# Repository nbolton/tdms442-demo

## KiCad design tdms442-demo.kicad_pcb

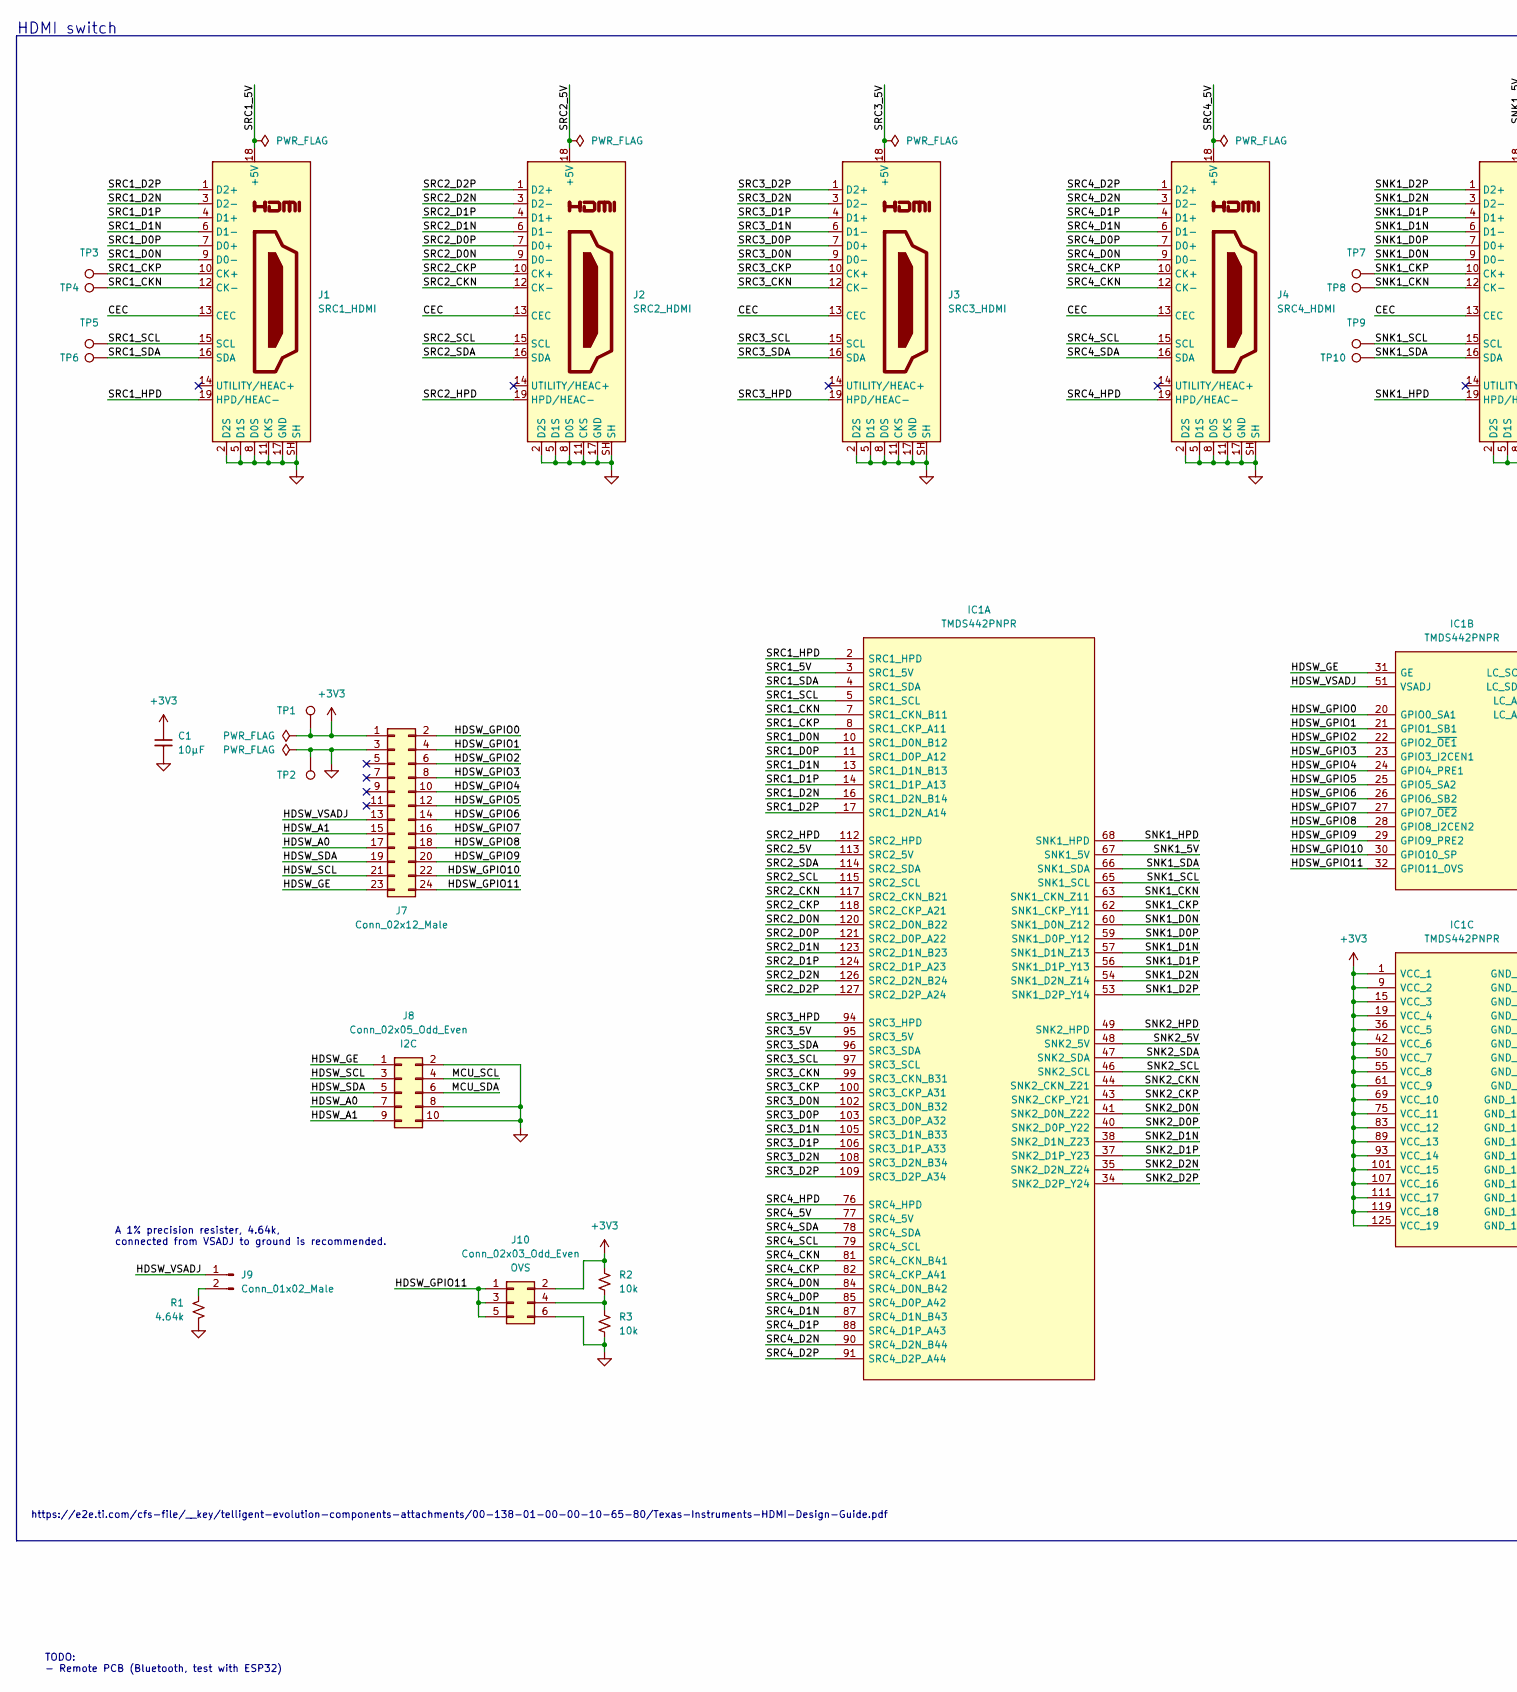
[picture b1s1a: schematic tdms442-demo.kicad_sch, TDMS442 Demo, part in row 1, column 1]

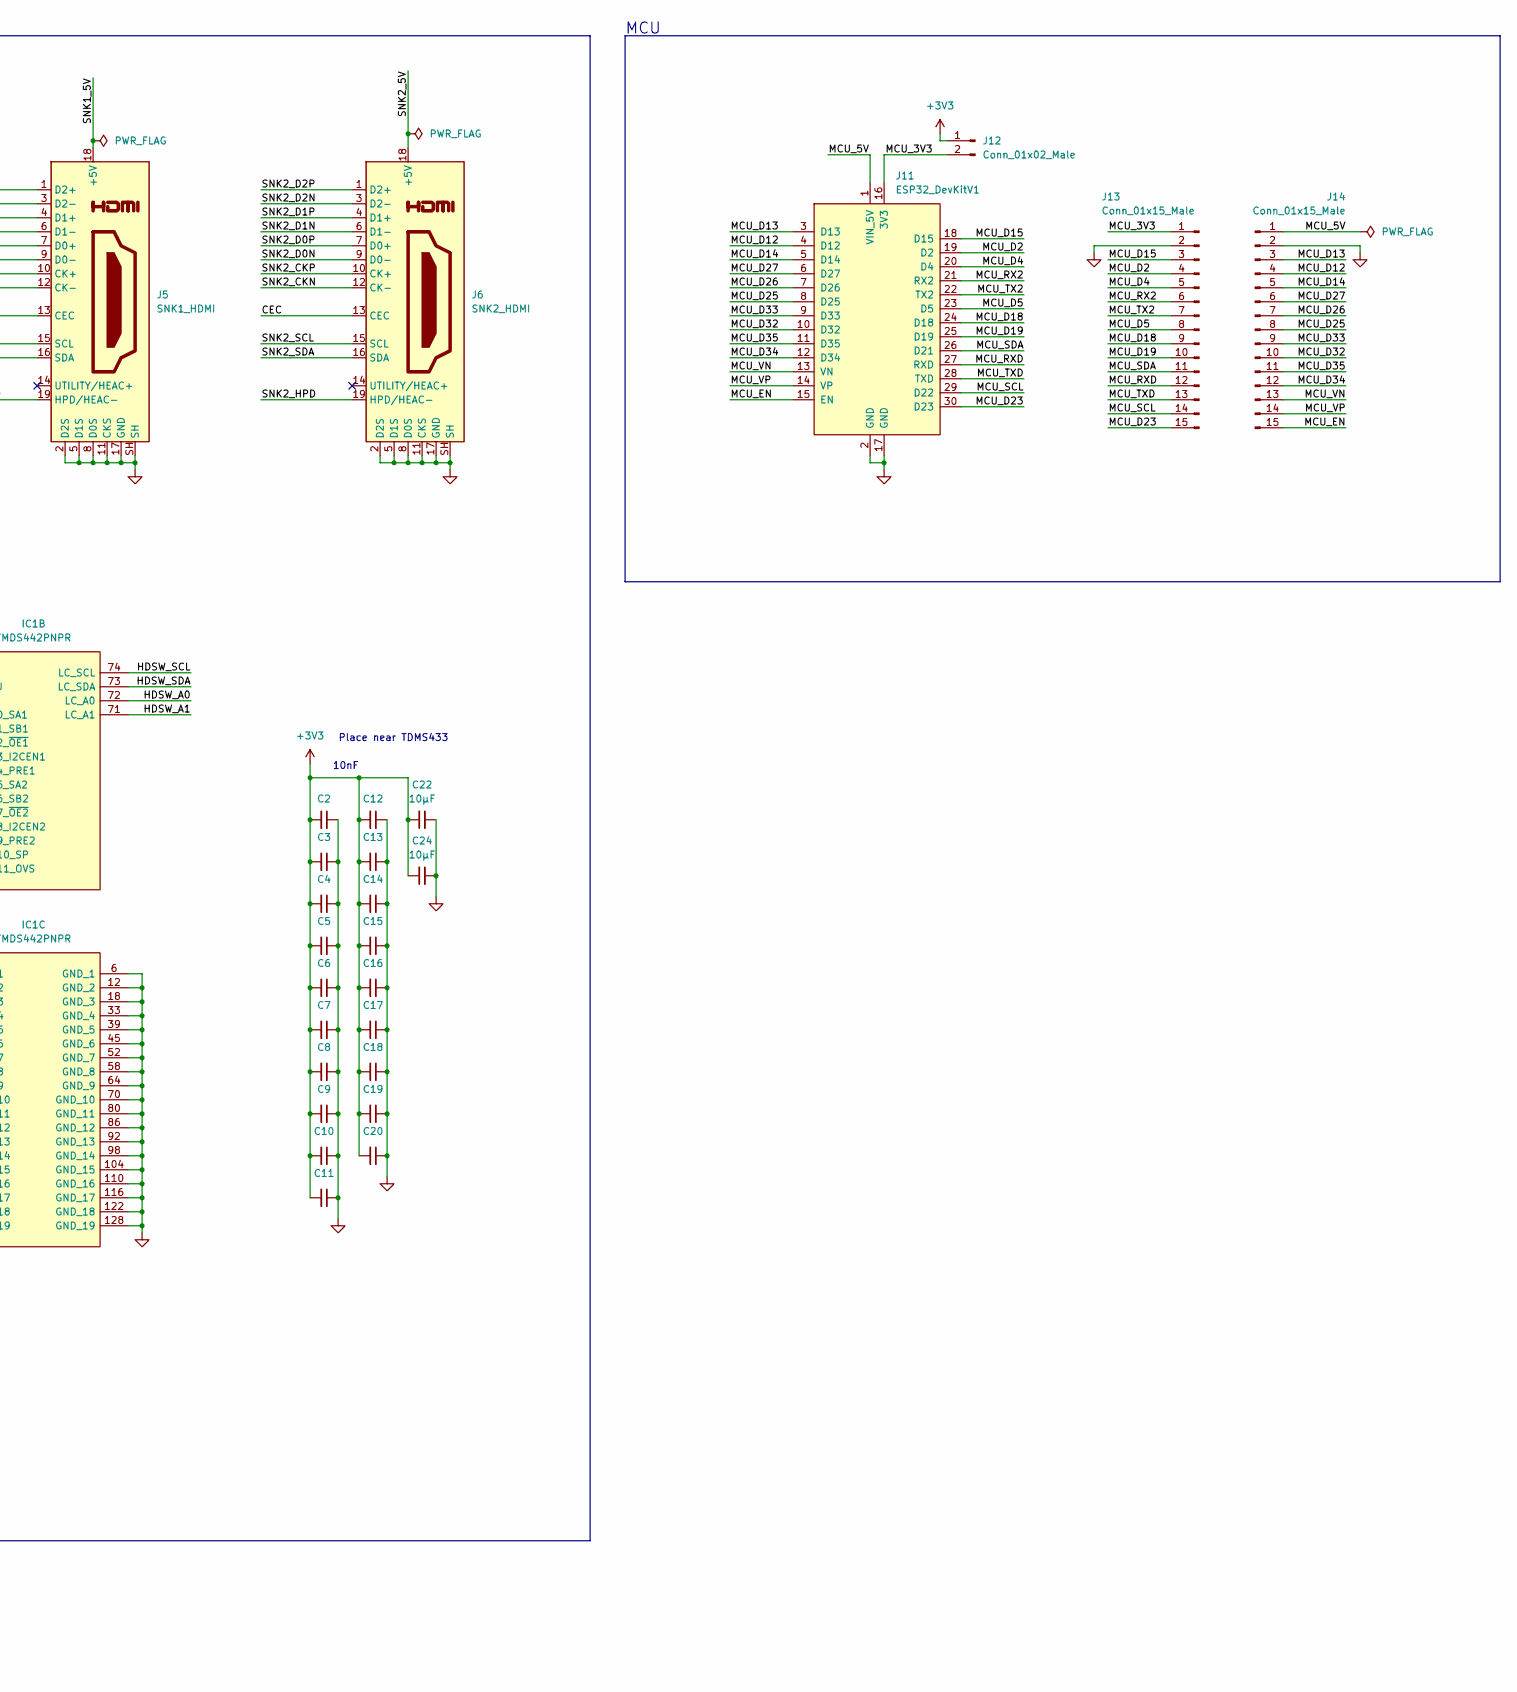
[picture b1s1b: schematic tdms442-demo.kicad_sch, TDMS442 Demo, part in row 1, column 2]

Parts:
C1, C22, C24: 10µF; C_0805_2012Metric_Pad1.18x1.45mm_HandSolder; LCSC Part C17024
C2, C3, C4, C5, C6, C7, C8, C9, C10, C11, C12, C13, C14, C15, C16, C17, C18, C19, C20: 10nF; C_0402_1005Metric_Pad0.74x0.62mm_HandSolder; LCSC Part C15195
IC1: TMDS442PNPR; TQFP-128-TI-PowerPAD; Mouser Part Number 595-TMDS442PNPR
J1: SRC1_HDMI; HDMI_A_Molex_208658-1001_Horizontal; LCSC Part C428484
J2: SRC2_HDMI; HDMI_A_Molex_208658-1001_Horizontal; LCSC Part C428484
J3: SRC3_HDMI; HDMI_A_Molex_208658-1001_Horizontal; LCSC Part C428484
J4: SRC4_HDMI; HDMI_A_Molex_208658-1001_Horizontal; LCSC Part C428484
J5: SNK1_HDMI; HDMI_A_Molex_208658-1001_Horizontal; LCSC Part C428484
J6: SNK2_HDMI; HDMI_A_Molex_208658-1001_Horizontal; LCSC Part C428484
J7: Conn_02x12_Male; PinHeader_2x12_P2.54mm_Vertical; LCSC Part C2894973
J8: Conn_02x05_Odd_Even; PinHeader_2x05_P2.54mm_Vertical; LCSC Part C2894966
J9, J12: Conn_01x02_Male; PinHeader_1x02_P2.54mm_Vertical; LCSC Part C2894925
J10: Conn_02x03_Odd_Even; PinHeader_2x03_P2.54mm_Vertical; LCSC Part C2894964
J11: ESP32_DevKitV1; PinSocket_ESP32_DevKitV1
J13, J14: Conn_01x15_Male; PinHeader_1x15_P2.54mm_Vertical; LCSC Part C124373
R1: 4.64k; R_0603_1608Metric_Pad0.98x0.95mm_HandSolder; LCSC Part C269427
R2, R3: 10k; R_0603_1608Metric_Pad0.98x0.95mm_HandSolder; LCSC Part C844727
TP1, TP2: TestPoint; TestPoint_Keystone_5019_Minature; LCSC Part C238131
TP3, TP4, TP5, TP6, TP7, TP8, TP9, TP10: TestPoint; TestPoint_Pad_1.0x1.0mm

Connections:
+3V3: C1.1, C2.2, C3.2, C4.2, C5.2, C6.2, C7.2, C8.2, C9.2, C10.2, C11.2, C12.2, C13.2, C14.2, C15.2, C16.2, C17.2, C18.2, C19.2, C20.2, C22.1, C24.1, IC1.1 (VCC_1), IC1.9 (VCC_2), IC1.15 (VCC_3), IC1.19 (VCC_4), IC1.36 (VCC_5), IC1.42 (VCC_6), IC1.50 (VCC_7), IC1.55 (VCC_8), IC1.61 (VCC_9), IC1.69 (VCC_10), IC1.75 (VCC_11), IC1.83 (VCC_12), IC1.89 (VCC_13), IC1.93 (VCC_14), IC1.101 (VCC_15), IC1.107 (VCC_16), IC1.111 (VCC_17), IC1.119 (VCC_18), IC1.125 (VCC_19), J7.1, J10.2, J12.1, R2.1, TP1.1
/CEC: J1.13 (CEC), J2.13 (CEC), J3.13 (CEC), J4.13 (CEC), J5.13 (CEC), J6.13 (CEC)
/HDSW_A0: IC1.72 (LC_A0), J7.17, J8.7
/HDSW_A1: IC1.71 (LC_A1), J7.15, J8.9
/HDSW_GE: IC1.31 (GE), J7.23, J8.1
/HDSW_GPIO0: IC1.20 (GPIO0_SA1), J7.2
/HDSW_GPIO1: IC1.21 (GPIO1_SB1), J7.4
/HDSW_GPIO2: IC1.22 (GPIO2_~OE1), J7.6
/HDSW_GPIO3: IC1.23 (GPIO3_I2CEN1), J7.8
/HDSW_GPIO4: IC1.24 (GPIO4_PRE1), J7.10
/HDSW_GPIO5: IC1.25 (GPIO5_SA2), J7.12
/HDSW_GPIO6: IC1.26 (GPIO6_SB2), J7.14
/HDSW_GPIO7: IC1.27 (GPIO7_~OE2), J7.16
/HDSW_GPIO8: IC1.28 (GPIO8_I2CEN2), J7.18
/HDSW_GPIO9: IC1.29 (GPIO9_PRE2), J7.20
/HDSW_GPIO10: IC1.30 (GPIO10_SP), J7.22
/HDSW_GPIO11: IC1.32 (GPIO11_OVS), J7.24, J10.1, J10.3, J10.5
/HDSW_SCL: IC1.74 (LC_SCL), J7.21, J8.3
/HDSW_SDA: IC1.73 (LC_SDA), J7.19, J8.5
/HDSW_VSADJ: IC1.51 (VSADJ), J7.13, J9.1
/MCU_3V3: J11.16 (3V3), J12.2, J13.1
/MCU_5V: J11.1 (VIN_5V), J14.1
/MCU_D2: J11.19 (D2), J13.4
/MCU_D4: J11.20 (D4), J13.5
/MCU_D5: J11.23 (D5), J13.8
/MCU_D12: J11.4 (D12), J14.4
/MCU_D13: J11.3 (D13), J14.3
/MCU_D14: J11.5 (D14), J14.5
/MCU_D15: J11.18 (D15), J13.3
/MCU_D18: J11.24 (D18), J13.9
/MCU_D19: J11.25 (D19), J13.10
/MCU_D23: J11.30 (D23), J13.15
/MCU_D25: J11.8 (D25), J14.8
/MCU_D26: J11.7 (D26), J14.7
/MCU_D27: J11.6 (D27), J14.6
/MCU_D32: J11.10 (D32), J14.10
/MCU_D33: J11.9 (D33), J14.9
/MCU_D34: J11.12 (D34), J14.12
/MCU_D35: J11.11 (D35), J14.11
/MCU_EN: J11.15 (EN), J14.15
/MCU_RX2: J11.21 (RX2), J13.6
/MCU_RXD: J11.27 (RXD), J13.12
/MCU_SCL: J8.4, J11.29 (D22), J13.14
/MCU_SDA: J8.6, J11.26 (D21), J13.11
/MCU_TX2: J11.22 (TX2), J13.7
/MCU_TXD: J11.28 (TXD), J13.13
/MCU_VN: J11.13 (VN), J14.13
/MCU_VP: J11.14 (VP), J14.14
/SNK1_5V: IC1.67 (SNK1_5V), J5.18 (+5V)
/SNK1_CKN: IC1.63 (SNK1_CKN_Z11), J5.12 (CK-), TP8.1
/SNK1_CKP: IC1.62 (SNK1_CKP_Y11), J5.10 (CK+), TP7.1
/SNK1_D0N: IC1.60 (SNK1_D0N_Z12), J5.9 (D0-)
/SNK1_D0P: IC1.59 (SNK1_D0P_Y12), J5.7 (D0+)
/SNK1_D1N: IC1.57 (SNK1_D1N_Z13), J5.6 (D1-)
/SNK1_D1P: IC1.56 (SNK1_D1P_Y13), J5.4 (D1+)
/SNK1_D2N: IC1.54 (SNK1_D2N_Z14), J5.3 (D2-)
/SNK1_D2P: IC1.53 (SNK1_D2P_Y14), J5.1 (D2+)
/SNK1_HPD: IC1.68 (SNK1_HPD), J5.19 (HPD/HEAC-)
/SNK1_SCL: IC1.65 (SNK1_SCL), J5.15 (SCL), TP9.1
/SNK1_SDA: IC1.66 (SNK1_SDA), J5.16 (SDA), TP10.1
/SNK2_5V: IC1.48 (SNK2_5V), J6.18 (+5V)
/SNK2_CKN: IC1.44 (SNK2_CKN_Z21), J6.12 (CK-)
/SNK2_CKP: IC1.43 (SNK2_CKP_Y21), J6.10 (CK+)
/SNK2_D0N: IC1.41 (SNK2_D0N_Z22), J6.9 (D0-)
/SNK2_D0P: IC1.40 (SNK2_D0P_Y22), J6.7 (D0+)
/SNK2_D1N: IC1.38 (SNK2_D1N_Z23), J6.6 (D1-)
/SNK2_D1P: IC1.37 (SNK2_D1P_Y23), J6.4 (D1+)
/SNK2_D2N: IC1.35 (SNK2_D2N_Z24), J6.3 (D2-)
/SNK2_D2P: IC1.34 (SNK2_D2P_Y24), J6.1 (D2+)
/SNK2_HPD: IC1.49 (SNK2_HPD), J6.19 (HPD/HEAC-)
/SNK2_SCL: IC1.46 (SNK2_SCL), J6.15 (SCL)
/SNK2_SDA: IC1.47 (SNK2_SDA), J6.16 (SDA)
/SRC1_5V: IC1.3 (SRC1_5V), J1.18 (+5V)
/SRC1_CKN: IC1.7 (SRC1_CKN_B11), J1.12 (CK-), TP4.1
/SRC1_CKP: IC1.8 (SRC1_CKP_A11), J1.10 (CK+), TP3.1
/SRC1_D0N: IC1.10 (SRC1_D0N_B12), J1.9 (D0-)
/SRC1_D0P: IC1.11 (SRC1_D0P_A12), J1.7 (D0+)
/SRC1_D1N: IC1.13 (SRC1_D1N_B13), J1.6 (D1-)
/SRC1_D1P: IC1.14 (SRC1_D1P_A13), J1.4 (D1+)
/SRC1_D2N: IC1.16 (SRC1_D2N_B14), J1.3 (D2-)
/SRC1_D2P: IC1.17 (SRC1_D2N_A14), J1.1 (D2+)
/SRC1_HPD: IC1.2 (SRC1_HPD), J1.19 (HPD/HEAC-)
/SRC1_SCL: IC1.5 (SRC1_SCL), J1.15 (SCL), TP5.1
/SRC1_SDA: IC1.4 (SRC1_SDA), J1.16 (SDA), TP6.1
/SRC2_5V: IC1.113 (SRC2_5V), J2.18 (+5V)
/SRC2_CKN: IC1.117 (SRC2_CKN_B21), J2.12 (CK-)
/SRC2_CKP: IC1.118 (SRC2_CKP_A21), J2.10 (CK+)
/SRC2_D0N: IC1.120 (SRC2_D0N_B22), J2.9 (D0-)
/SRC2_D0P: IC1.121 (SRC2_D0P_A22), J2.7 (D0+)
/SRC2_D1N: IC1.123 (SRC2_D1N_B23), J2.6 (D1-)
/SRC2_D1P: IC1.124 (SRC2_D1P_A23), J2.4 (D1+)
/SRC2_D2N: IC1.126 (SRC2_D2N_B24), J2.3 (D2-)
/SRC2_D2P: IC1.127 (SRC2_D2P_A24), J2.1 (D2+)
/SRC2_HPD: IC1.112 (SRC2_HPD), J2.19 (HPD/HEAC-)
/SRC2_SCL: IC1.115 (SRC2_SCL), J2.15 (SCL)
/SRC2_SDA: IC1.114 (SRC2_SDA), J2.16 (SDA)
/SRC3_5V: IC1.95 (SRC3_5V), J3.18 (+5V)
/SRC3_CKN: IC1.99 (SRC3_CKN_B31), J3.12 (CK-)
/SRC3_CKP: IC1.100 (SRC3_CKP_A31), J3.10 (CK+)
/SRC3_D0N: IC1.102 (SRC3_D0N_B32), J3.9 (D0-)
/SRC3_D0P: IC1.103 (SRC3_D0P_A32), J3.7 (D0+)
/SRC3_D1N: IC1.105 (SRC3_D1N_B33), J3.6 (D1-)
/SRC3_D1P: IC1.106 (SRC3_D1P_A33), J3.4 (D1+)
/SRC3_D2N: IC1.108 (SRC3_D2N_B34), J3.3 (D2-)
/SRC3_D2P: IC1.109 (SRC3_D2P_A34), J3.1 (D2+)
/SRC3_HPD: IC1.94 (SRC3_HPD), J3.19 (HPD/HEAC-)
/SRC3_SCL: IC1.97 (SRC3_SCL), J3.15 (SCL)
/SRC3_SDA: IC1.96 (SRC3_SDA), J3.16 (SDA)
/SRC4_5V: IC1.77 (SRC4_5V), J4.18 (+5V)
/SRC4_CKN: IC1.81 (SRC4_CKN_B41), J4.12 (CK-)
/SRC4_CKP: IC1.82 (SRC4_CKP_A41), J4.10 (CK+)
/SRC4_D0N: IC1.84 (SRC4_D0N_B42), J4.9 (D0-)
/SRC4_D0P: IC1.85 (SRC4_D0P_A42), J4.7 (D0+)
/SRC4_D1N: IC1.87 (SRC4_D1N_B43), J4.6 (D1-)
/SRC4_D1P: IC1.88 (SRC4_D1P_A43), J4.4 (D1+)
/SRC4_D2N: IC1.90 (SRC4_D2N_B44), J4.3 (D2-)
/SRC4_D2P: IC1.91 (SRC4_D2P_A44), J4.1 (D2+)
/SRC4_HPD: IC1.76 (SRC4_HPD), J4.19 (HPD/HEAC-)
/SRC4_SCL: IC1.79 (SRC4_SCL), J4.15 (SCL)
/SRC4_SDA: IC1.78 (SRC4_SDA), J4.16 (SDA)
GND: C1.2, C2.1, C3.1, C4.1, C5.1, C6.1, C7.1, C8.1, C9.1, C10.1, C11.1, C12.1, C13.1, C14.1, C15.1, C16.1, C17.1, C18.1, C19.1, C20.1, C22.2, C24.2, IC1.6 (GND_1), IC1.12 (GND_2), IC1.18 (GND_3), IC1.33 (GND_4), IC1.39 (GND_5), IC1.45 (GND_6), IC1.52 (GND_7), IC1.58 (GND_8), IC1.64 (GND_9), IC1.70 (GND_10), IC1.80 (GND_11), IC1.86 (GND_12), IC1.92 (GND_13), IC1.98 (GND_14), IC1.104 (GND_15), IC1.110 (GND_16), IC1.116 (GND_17), IC1.122 (GND_18), IC1.128 (GND_19), J1.2 (D2S), J1.5 (D1S), J1.8 (D0S), J1.11 (CKS), J1.17 (GND), J1.SH, J2.2 (D2S), J2.5 (D1S), J2.8 (D0S), J2.11 (CKS), J2.17 (GND), J2.SH, J3.2 (D2S), J3.5 (D1S), J3.8 (D0S), J3.11 (CKS), J3.17 (GND), J3.SH, J4.2 (D2S), J4.5 (D1S), J4.8 (D0S), J4.11 (CKS), J4.17 (GND), J4.SH, J5.2 (D2S), J5.5 (D1S), J5.8 (D0S), J5.11 (CKS), J5.17 (GND), J5.SH, J6.2 (D2S), J6.5 (D1S), J6.8 (D0S), J6.11 (CKS), J6.17 (GND), J6.SH, J7.3, J8.2, J8.8, J8.10, J10.6, J11.2 (GND), J11.17 (GND), J13.2, J14.2, R1.2, R3.2, TP2.1
unnamed: J9.2, R1.1
unnamed: J10.4, R2.2, R3.1

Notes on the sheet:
10nF
Place near TDMS433
TODO: - Remote PCB (Bluetooth, test with ESP32)
https://e2e.ti.com/cfs-file/__key/telligent-evolution-components-attachments/00-138-01-00-00-10-65-80/Texas-Instruments-HDMI-Design-Guide.pdf
HDMI switch
MCU
A 1% precision resister, 4.64k, connected from VSADJ to ground is recommended.

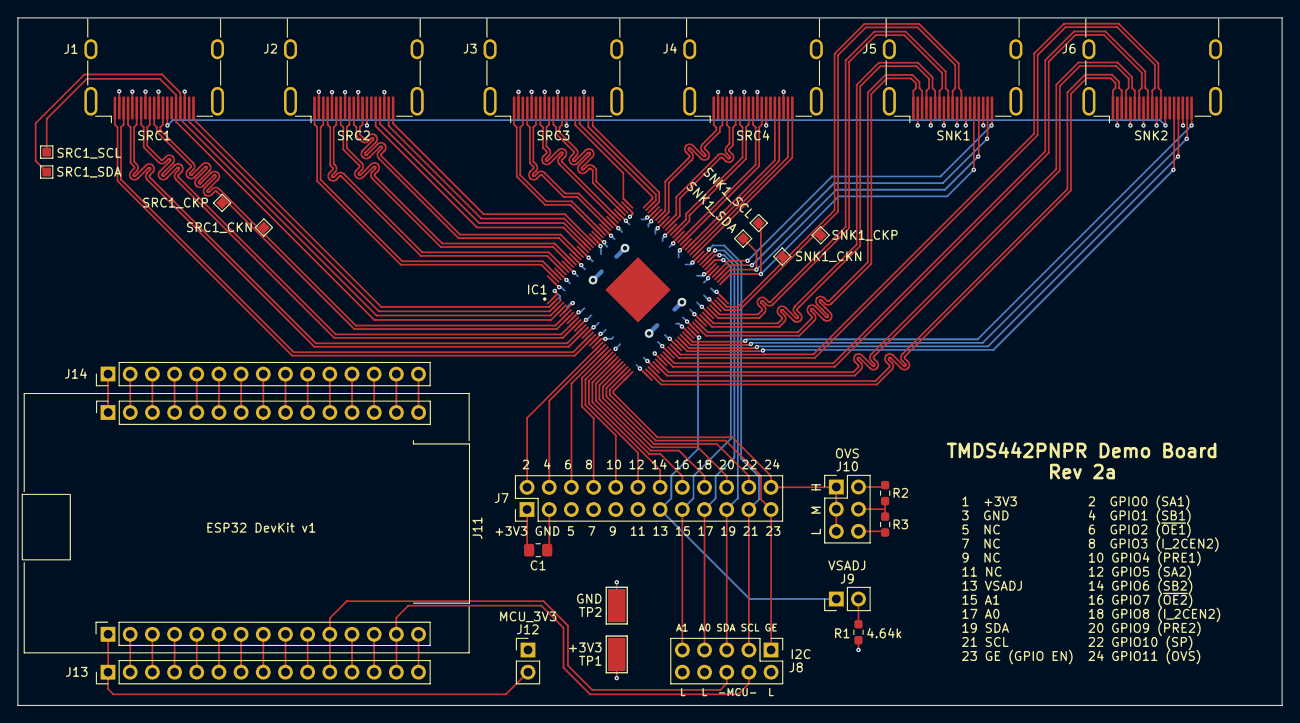
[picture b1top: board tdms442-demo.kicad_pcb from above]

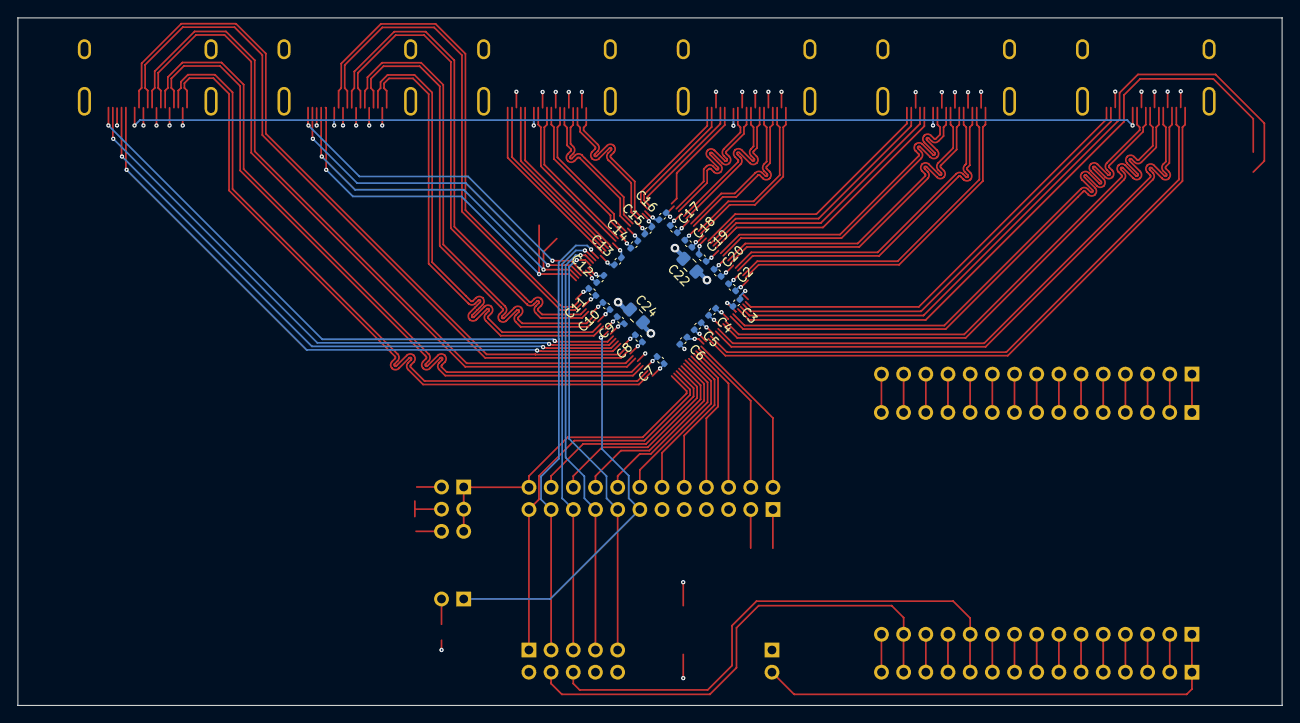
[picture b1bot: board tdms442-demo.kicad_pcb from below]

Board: 4 copper layers, 144.8 x 78.7 mm, 50 parts (21 on the bottom side), 123 nets.

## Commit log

2024-09-21 First public copy
